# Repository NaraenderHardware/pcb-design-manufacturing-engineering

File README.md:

# PCB Design and Manufacturing Engineering

**Author:** Naraender S  
**License:** [MIT License](LICENSE)  

---

## 1. Overview and Project Scope

This repository documents my engineering work in printed circuit board (PCB) design, schematic capture, circuit calculations, and physical prototyping. It contains four hardware case studies developed using KiCad and practical laboratory fabrication methods:

1. **5V Regulated Through-Hole Power Supply (`designs/general-pcb-design`):** A single-sided linear DC power supply built with through-hole components (LM7805, 1N4007 bridge rectifier, and electrolytic filtering) designed for reliable hand assembly.
2. **Multi-Rail SMD Linear Power Supply (`designs/smd-pcb-design`):** A compact 2-layer surface-mount power distribution board designed to provide +5V, +12V, and -12V rails using TO-252 (DPAK) regulators. *Note: An audit identified a schematic power-rail short in the original design; manufacturing outputs are quarantined, and a preliminary Revision A schematic draft is provided.*
3. **ATtiny85 USB Breakout Dongle (`designs/usb-pcb-design`):** A standalone 2-layer USB development dongle based on the Microchip ATtiny85-20S microcontroller with PCB edge contacts for USB Type-A ports, 3.6V Zener level clamping, and breakout pin headers.
4. **Chemical-Etched Multi-Rail Power Supply Bench Study (`designs/linear-regulator-design`):** A hands-on prototyping project from a hardware workshop demonstrating manual single-sided PCB fabrication using ferric chloride ($FeCl_3$) chemical wet etching, with design calculations and recorded multimeter test readings.

---

## 2. Summary of Case Studies

| Case Study | Architecture / Function | Dimensions | Layer Count | Components | Status Summary | Documentation Link |
| :--- | :--- | :--- | :--- | :--- | :--- | :--- |
| **General THT PCB** | 5V 1.5A Regulated Linear Power Supply | 95.00 x 33.50 mm | 1 Copper Layer (`B.Cu`), 1.6 mm FR4 | 12 parts / 4 mounting holes | Schematic & layout complete; static clearances clean; native ERC/DRC and drill files pending | [Case Study 1 Readme](designs/general-pcb-design/README.md) |
| **SMD Multi-Rail PCB** | Triple-Output (+5V, +12V, -12V) SMD Supply | 33.50 x 30.00 mm | 2 Layers (`F.Cu`, `B.Cu`), 1.6 mm FR4 | 22 parts (DPAK, SMA, 0805) | Critical power-rail short identified; Gerbers quarantined; Revision A is an unverified draft | [Case Study 2 Readme](designs/smd-pcb-design/README.md) |
| **USB ATtiny85 PCB** | ATtiny85-20S USB Breakout Dongle (Standalone) | 40.00 x 12.20 mm | 2 Layers (`F.Cu`, `B.Cu`), 1.6 mm FR4 | 12 parts (SOIC-8, SOD-123) | Schematic & layout complete; static clearances clean; native ERC/DRC and hardware USB checks pending | [Case Study 3 Readme](designs/usb-pcb-design/README.md) |
| **Linear Regulator Bench** | Chemical-Etched (+5V, &plusmn;12V) Bench Prototype | ~100 x 60 mm (Bench) | 1 Layer (Copper-clad single-sided) | Discrete bench parts | Physical workshop prototype; multimeter test readings documented; no digital CAD files | [Case Study 4 Readme](designs/linear-regulator-design/README.md) |

---

## 3. Design Previews and Available Assets

### Case Study 1: 5V Regulated Through-Hole Power Supply
| PCB Layout Preview | Schematic Preview |
| :---: | :---: |
|  |  |

- Schematic: [designs/general-pcb-design/HARDWARE/Kicad-Hardware-Design.kicad_sch](designs/general-pcb-design/HARDWARE/Kicad-Hardware-Design.kicad_sch)
- PCB Layout: [designs/general-pcb-design/HARDWARE/Kicad-Hardware-Design.kicad_pcb](designs/general-pcb-design/HARDWARE/Kicad-Hardware-Design.kicad_pcb)
- Bill of Materials: [designs/general-pcb-design/BOM/bom.csv](designs/general-pcb-design/BOM/bom.csv)
- Bottom Copper Gerber: [designs/general-pcb-design/GERBER/Kicad-Hardware-Design-B_Cu.gbr](designs/general-pcb-design/GERBER/Kicad-Hardware-Design-B_Cu.gbr)

---

### Case Study 2: Multi-Rail SMD Linear Power Supply
| PCB Layout Preview | Schematic Preview |
| :---: | :---: |
|  |  |

- Schematic (Original): [designs/smd-pcb-design/HARDWARE/GitHub2.kicad_sch](designs/smd-pcb-design/HARDWARE/GitHub2.kicad_sch)
- PCB Layout (Original): [designs/smd-pcb-design/HARDWARE/GitHub2.kicad_pcb](designs/smd-pcb-design/HARDWARE/GitHub2.kicad_pcb)
- Bill of Materials: [designs/smd-pcb-design/BOM/bom.csv](designs/smd-pcb-design/BOM/bom.csv)
- Gerber Job File (Quarantined): [designs/smd-pcb-design/GERBER/GitHub2-job.gbrjob](designs/smd-pcb-design/GERBER/GitHub2-job.gbrjob)
- Corrected Draft Schematic: [designs/smd-pcb-design/revA_corrected/HARDWARE/GitHub2_revA_corrected.kicad_sch](designs/smd-pcb-design/revA_corrected/HARDWARE/GitHub2_revA_corrected.kicad_sch)
- Detailed Defect Analysis: [designs/smd-pcb-design/revA_corrected/README.md](designs/smd-pcb-design/revA_corrected/README.md)

---

### Case Study 3: ATtiny85 USB Breakout Dongle
| PCB Layout Preview | Schematic Preview |
| :---: | :---: |
|  |  |

- Schematic: [designs/usb-pcb-design/HARDWARE/USB.kicad_sch](designs/usb-pcb-design/HARDWARE/USB.kicad_sch)
- PCB Layout: [designs/usb-pcb-design/HARDWARE/USB.kicad_pcb](designs/usb-pcb-design/HARDWARE/USB.kicad_pcb)
- Bill of Materials: [designs/usb-pcb-design/BOM/bom.csv](designs/usb-pcb-design/BOM/bom.csv)
- Gerber Job File: [designs/usb-pcb-design/GERBER/USB-job.gbrjob](designs/usb-pcb-design/GERBER/USB-job.gbrjob)

---

### Case Study 4: Chemical-Etched Multi-Rail Power Supply Bench Study

- Design Calculations: [designs/linear-regulator-design/regulator-design/docs/calculations.md](designs/linear-regulator-design/regulator-design/docs/calculations.md)
- Circuit Working Principles: [designs/linear-regulator-design/regulator-design/docs/working.md](designs/linear-regulator-design/regulator-design/docs/working.md)
- Measured Multimeter Readings: [designs/linear-regulator-design/regulator-design/results/readings.txt](designs/linear-regulator-design/regulator-design/results/readings.txt)
- Etching Procedure: [designs/linear-regulator-design/pcb-etching/README.md](designs/linear-regulator-design/pcb-etching/README.md)

---

## 4. Tools, File Formats, and Verification Status

### Confirmed Tools and File Formats
- **KiCad 9:** Used for schematic capture (`.kicad_sch`) and board layout (`.kicad_pcb`).
- **Gerber Files:** Standard RS-274X copper layers (`.gbr`) and Gerber job manifests (`.gbrjob`).
- **Component Data:** Comma-separated Bill of Materials (`.csv`).
- **Vector Previews:** Scalable Vector Graphics (`.svg`) generated directly from CAD layout coordinates.
- **Documentation and Bench Data:** Markdown engineering notes (`.md`) and raw test logs (`.txt`).

### Verification Status and Known Limitations
- **SMD Board Power-Rail Short (Critical Defect):**
  - An unintentional vertical wire (UUID `b3812738-1a62-4d38-bef5-d9db1e02c554`) connects coordinate `(45.72, 35.56)` on the positive DC bus directly to `(45.72, 27.94)` on the 7805 return line in `designs/smd-pcb-design/HARDWARE/GitHub2.kicad_sch`.
  - This short ties regulator `U1` (L7805) input and ground together and shorts filter capacitor `C1`.
  - The board layout in `GitHub2.kicad_pcb` physically routes this shorted net.
  - **The associated manufacturing files are quarantined and must not be used for fabrication.**
  - A preliminary corrected schematic draft is provided in `revA_corrected/`. Excising the shorting wire leaves the 7805 return line floating relative to common ground; this draft remains unverified until connected in KiCad and re-routed on the PCB.
- **Native KiCad ERC and DRC Checks:**
  - KiCad was not installed in the review environment. Python static checks confirmed basic 2D Euclidean clearances between linear copper traces and circular pads, but these do not replace native KiCad Electrical Rules Check (ERC) or Design Rules Check (DRC).
  - Native KiCad ERC and DRC must be executed prior to any commercial manufacturing sign-off.
- **Manufacturing Deliverables:**
  - Complete drill files (`*.drl`), solder mask, and silkscreen Gerber layers are not present locally for the through-hole and USB boards.
- **ATtiny85 USB Dongle Considerations:**
  - The microcontroller uses an internal calibrated RC oscillator. Low-Speed USB 1.1 requires +/-1.5% frequency accuracy, which typically requires runtime software calibration against USB frame packets.
  - The PCB edge connector is designed on 1.60 mm FR4, which may fit loosely in standard USB-A ports (typically expecting a 2.0 mm to 2.4 mm plug tongue).
- **Chemical-Etched Power Supply:**
  - Preserved strictly as a documented hands-on workshop build with recorded multimeter readings; no digital CAD schematic or layout files exist in this repository.

A complete audit log of file hashes, clearance checks, and defect traces is documented in [docs/PORTFOLIO_VERIFICATION.md](docs/PORTFOLIO_VERIFICATION.md).

---

## 5. Repository Structure

```
01_PCB_Design_and_Manufacturing_Engineering/
|-- .gitignore                                    # Excludes editor caches, KiCad backups, and temporary files
|-- LICENSE                                       # MIT License (Naraender S 2025)
|-- README.md                                     # Main repository overview and index
|-- assets/                                       # Vector SVG previews for schematics and layouts
|   |-- general_pcb_layout.svg
|   |-- general_schematic.svg
|   |-- smd_pcb_layout.svg
|   |-- smd_schematic.svg
|   |-- usb_pcb_layout.svg
|   |-- usb_schematic.svg
|   `-- linear_regulator_architecture.svg
|-- docs/
|   `-- PORTFOLIO_VERIFICATION.md                 # Detailed engineering verification report
`-- designs/
    |-- general-pcb-design/                       # Case Study 1: 5V Through-Hole Linear Supply
    |   |-- .gitignore
    |   |-- LICENSE
    |   |-- HISTORICAL_NOTES.md
    |   |-- README.md
    |   |-- pcb_layout.svg & schematic.svg
    |   |-- BOM/bom.csv
    |   |-- GERBER/
    |   |   |-- Kicad-Hardware-Design-B_Cu.gbr
    |   |   `-- Kicad-Hardware-Design-job.gbrjob
    |   `-- HARDWARE/
    |       |-- Kicad-Hardware-Design.kicad_pcb
    |       `-- Kicad-Hardware-Design.kicad_sch
    |-- smd-pcb-design/                           # Case Study 2: Multi-Rail SMD Supply (Defect Documented)
    |   |-- HISTORICAL_NOTES.md
    |   |-- README.md
    |   |-- pcb_layout.svg & schematic.svg
    |   |-- BOM/bom.csv
    |   |-- GERBER/GitHub2-job.gbrjob             # Quarantined manufacturing file
    |   |-- HARDWARE/
    |   |   |-- GitHub2.kicad_pcb
    |   |   `-- GitHub2.kicad_sch
    |   `-- revA_corrected/                       # Unverified Revision A draft schematic
    |       |-- README.md
    |       `-- HARDWARE/GitHub2_revA_corrected.kicad_sch
    |-- usb-pcb-design/                           # Case Study 3: ATtiny85 USB Breakout Dongle
    |   |-- .gitignore
    |   |-- README.md
    |   |-- pcb_layout.svg & schematic.svg
    |   |-- BOM/bom.csv
    |   |-- GERBER/USB-job.gbrjob
    |   `-- HARDWARE/
    |       |-- USB.kicad_pcb
    |       `-- USB.kicad_sch
    `-- linear-regulator-design/                  # Case Study 4: Chemical-Etched Bench Prototype
        |-- HISTORICAL_NOTES.md
        |-- README.md
        |-- architecture.svg
        |-- pcb-etching/
        |   `-- README.md                         # Step-by-step chemical etching guide
        `-- regulator-design/
            |-- README.md
            |-- docs/calculations.md              # Circuit calculations and thermal formulas
            |-- docs/working.md                   # Stage-by-stage circuit operation
            `-- results/readings.txt              # Multimeter voltage readings
```

---

## 6. License

This project and all hardware designs, documentation, and test logs are licensed under the [MIT License](LICENSE).  
Copyright &copy; 2025 **Naraender S**.

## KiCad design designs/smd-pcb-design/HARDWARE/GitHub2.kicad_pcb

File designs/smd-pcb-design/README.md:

# Case Study 2: Multi-Rail SMD Linear Power Supply

**Design Type:** Multi-Rail Linear Power Distribution (Surface-Mount)  
**CAD Tool:** KiCad  
**Status:** Defect identified during audit; manufacturing outputs quarantined; Revision A is an unverified draft schematic  

---

## 1. Overview and Design Purpose

This project is a surface-mount power supply board designed to deliver three regulated DC voltage rails: +5V, +12V, and -12V in a compact 33.5 mm x 30.0 mm footprint. The intended architecture takes a dual-polarity center-tapped AC transformer input or dual-polarity DC input to drive:
- An **L7805** regulator for a +5V logic rail
- An **L7812** regulator for a +12V analog/relay rail
- An **L7912** regulator for a -12V negative rail (such as for dual-supply operational amplifiers)

All three regulators use surface-mount DPAK (TO-252) packages, paired with SMA rectifier diodes and SMD electrolytic capacitors to keep the board compact.

---

## 2. Circuit Architecture and Schematics

### Schematic Preview

The schematic uses a 3-pin input header (`J1`), a 4-diode rectifier bridge (`D1`–`D4`), bulk filter capacitors (`C1`, `C2`, `C3`), high-frequency ceramic bypass capacitors (`C4`, `C5`, `C6`), three linear regulators (`U1`, `U2`, `U3`), output filter capacitors (`C7`–`C12`), and JST-PH output headers (`J2`, `J3`).

---

## 3. PCB Layout Architecture

### PCB Layout Preview

- **Dimensions:** 33.50 mm x 30.00 mm (finished profile 33.55 mm x 30.05 mm)
- **Layer Count:** 2 copper layers (`F.Cu`, `B.Cu`)
- **Substrate Thickness:** 1.60 mm FR4
- **Vias:** 16 interlayer vias (0.60 mm pad diameter, 0.30 mm finished drill hole)

---

## 4. Defect Analysis: Power-Rail Short Circuit

During an engineering audit of the design files, a critical schematic drafting mistake was identified that propagated directly into the PCB layout:

### Description of the Defect
In the original schematic file (`HARDWARE/GitHub2.kicad_sch`), an unintended vertical wire segment was drawn at `x=45.72` between `y=35.56` and `y=27.94` (UUID `b3812738-1a62-4d38-bef5-d9db1e02c554`):
- Point `(45.72, 35.56)` lies on the unregulated positive DC rail feeding regulator `U2` (L7812) from diode bridge cathodes `D1`/`D3`.
- Point `(45.72, 27.94)` lies on the ground return line for regulator `U1` (L7805).
- Because this vertical wire connected the two lines, KiCad merged the unregulated positive rail and the 7805 return line into a single net: `Net-(D1-K)`.

### Impact on Layout and Physical Circuit
1. **Regulator `U1` (L7805):** Pin 1 (Vin) and Pin 2 (GND) are shorted together on the same net.
2. **Capacitor `C1` (Bulk Filter):** Both positive and negative terminals are connected to `Net-(D1-K)`, shorting the capacitor across its terminals.
3. **Capacitor `C4` (Ceramic Bypass):** Both terminals are tied to `Net-(D1-K)`.
4. **Output Capacitors `C7` and `C10`:** Ground return terminals are tied to raw positive DC rather than common ground.
5. **Connector `J2` (5V Output):** Pin 2 (return) is tied to raw positive DC.
6. **Rectifier Stage:** Diodes `D1` and `D3` discharge directly into the 7805 return line.

### Manufacturing and Safety Impact
If this board were fabricated and powered as routed:
- It would present a direct dead short across the rectified DC power source.
- Diodes would fail from overcurrent, copper traces could burn, or the power supply would trigger overcurrent protection.
- **Quarantine Notice:** The Gerber files in `GERBER/` are **quarantined and must not be used for fabrication**.

---

## 5. Revision A Draft and Current Status

To preserve the authentic historical design files, the original schematic and PCB files in `HARDWARE/` remain completely unchanged.

A preliminary corrected schematic is provided in `revA_corrected/`:
- **File:** [revA_corrected/HARDWARE/GitHub2_revA_corrected.kicad_sch](revA_corrected/HARDWARE/GitHub2_revA_corrected.kicad_sch)
- **Detailed Documentation:** [revA_corrected/README.md](revA_corrected/README.md)
- **Change Made:** The vertical shorting wire (UUID `b3812738-1a62-4d38-bef5-d9db1e02c554`) was excised, restoring the continuous positive rail feeding `U2`.

### Remaining Unresolved Issues in Revision A
1. **Floating Return Rail:** Excising the shorting wire eliminates the dead short, but leaves the 7805 return rail (`y=27.94`) completely floating with no electrical connection to the Common Ground rail (`y=49.53`).
2. **PCB Layout Unchanged:** Modifying the schematic does not automatically reroute the copper traces in `HARDWARE/GitHub2.kicad_pcb`. The physical board layout still contains shorted copper traces.
3. **Draft Status:** Revision A is an **unverified draft**. Before this board can be fabricated, the return rail must be connected to ground in KiCad, traces must be rerouted in the PCB editor, and native ERC and DRC checks must pass.

---

## 6. Bill of Materials

| Reference | Quantity | Value | Package / Footprint | Description |
| :--- | :--- | :--- | :--- | :--- |
| `C1, C2, C3, C7, C8, C9` | 6 | Polarized Cap (SMD) | `Capacitor_SMD:CP_Elec_6.3x5.8` | Bulk filtering per voltage rail |
| `C4, C5, C6, C10, C11, C12` | 6 | Ceramic Cap (SMD) | `Capacitor_SMD:C_0805_2012Metric` | High-frequency bypass per rail |
| `D1, D2, D3, D4` | 4 | 1N4007 (SMD) | `Diode_SMD:D_SMA` | 1A 1000V Rectifier diodes |
| `J1, J3` | 2 | Conn_01x03 | `Connector_JST:JST_PH_S3B-PH-SM4-TB_1x03` | 3-pin JST-PH power interface |
| `J2` | 1 | Conn_01x02 | `Connector_JST:JST_PH_S2B-PH-SM4-TB_1x02` | 2-pin JST-PH 5V output interface |
| `U1` | 1 | L7805 | `Package_TO_SOT_SMD:TO-252-2` | +5V SMD linear regulator (DPAK) |
| `U2` | 1 | L7812 | `Package_TO_SOT_SMD:TO-252-2` | +12V SMD linear regulator (DPAK) |
| `U3` | 1 | L7912 | `Package_TO_SOT_SMD:TO-252-2` | -12V SMD linear regulator (DPAK) |

---

## 7. Project Files

- Original Schematic: [HARDWARE/GitHub2.kicad_sch](HARDWARE/GitHub2.kicad_sch)
- Original PCB Layout: [HARDWARE/GitHub2.kicad_pcb](HARDWARE/GitHub2.kicad_pcb)
- Bill of Materials: [BOM/bom.csv](BOM/bom.csv)
- Gerber Job File (Quarantined): [GERBER/GitHub2-job.gbrjob](GERBER/GitHub2-job.gbrjob)
- Historical Design Notes: [HISTORICAL_NOTES.md](HISTORICAL_NOTES.md)
- Corrected Revision A Draft: [revA_corrected/README.md](revA_corrected/README.md)

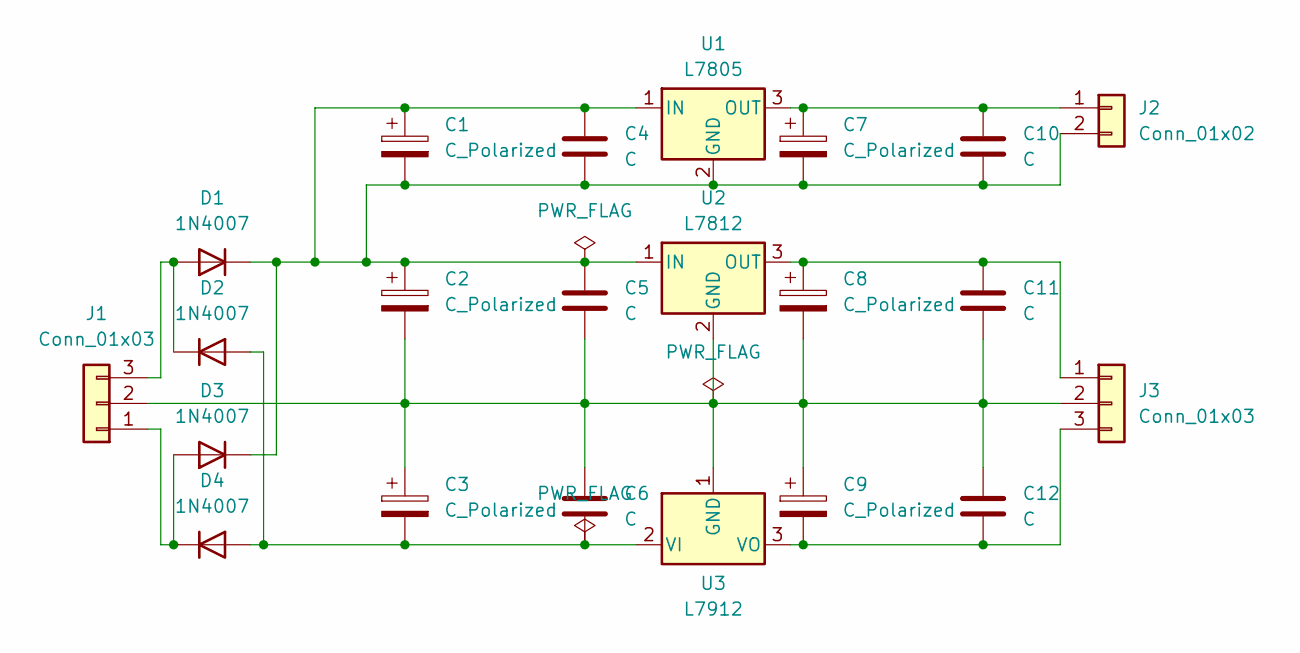
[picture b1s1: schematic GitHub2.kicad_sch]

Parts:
C1, C2, C3, C7, C8, C9: C_Polarized; CP_Elec_6.3x5.8
C4, C5, C6, C10, C11, C12: C; C_0805_2012Metric
D1, D2, D3, D4: 1N4007; D_SMA
J1, J3: Conn_01x03; JST_PH_S3B-PH-SM4-TB_1x03-1MP_P2.00mm_Horizontal
J2: Conn_01x02; JST_PH_S2B-PH-SM4-TB_1x02-1MP_P2.00mm_Horizontal
U1: L7805; TO-252-2
U2: L7812; TO-252-2
U3: L7912; TO-252-2

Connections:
unnamed: D1.2 (A), D2.1 (K), J1.3
unnamed: C1.1, C1.2, C2.1, C4.1, C4.2, C5.1, C7.2, C10.2, D1.1 (K), D3.1 (K), J2.2, U1.1 (IN), U1.2 (GND), U2.1 (IN)
unnamed: C3.2, C6.2, D2.2 (A), D4.2 (A), U3.2 (VI)
unnamed: D3.2 (A), D4.1 (K), J1.1
unnamed: C2.2, C3.1, C5.2, C6.1, C8.2, C9.1, C11.2, C12.1, J1.2, J3.2, U2.2 (GND), U3.1 (GND)
unnamed: C7.1, C10.1, J2.1, U1.3 (OUT)
unnamed: C8.1, C11.1, J3.1, U2.3 (OUT)
unnamed: C9.2, C12.2, J3.3, U3.3 (VO)

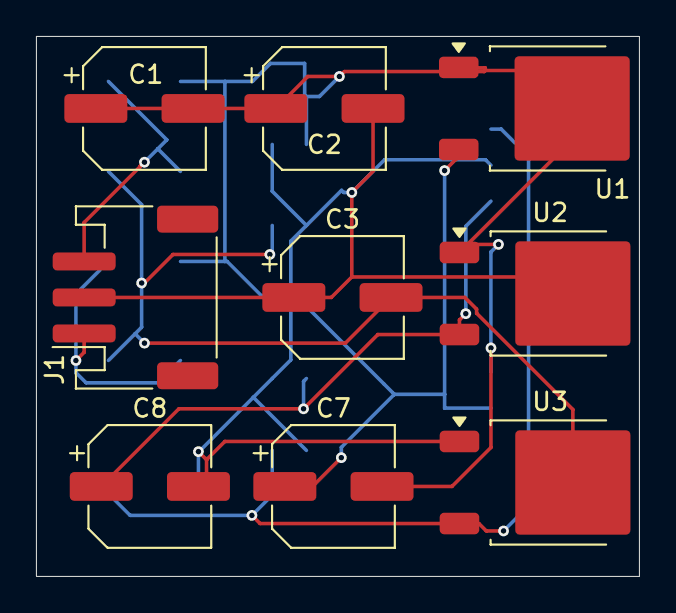
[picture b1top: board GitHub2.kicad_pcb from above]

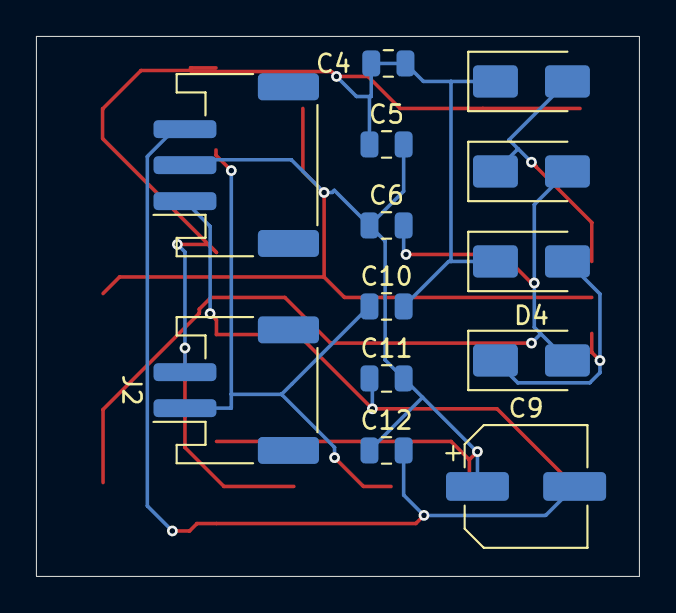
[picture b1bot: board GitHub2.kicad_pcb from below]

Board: 2 copper layers, 33.5 x 30.0 mm, 22 parts (13 on the bottom side), 8 nets.

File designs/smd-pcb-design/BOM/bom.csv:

"Reference","Qty","Value","DNP","Exclude from BOM","Exclude from Board","Footprint","Datasheet"
"C1,C2,C3,C7,C8,C9","6","C_Polarized","","","","Capacitor_SMD:CP_Elec_6.3x5.8","~"
"C4,C5,C6,C10,C11,C12","6","C","","","","Capacitor_SMD:C_0805_2012Metric","~"
"D1,D2,D3,D4","4","1N4007","","","","Diode_SMD:D_SMA","http://www.vishay.com/docs/88503/1n4001.pdf"
"J1,J3","2","Conn_01x03","","","","Connector_JST:JST_PH_S3B-PH-SM4-TB_1x03-1MP_P2.00mm_Horizontal","~"
"J2","1","Conn_01x02","","","","Connector_JST:JST_PH_S2B-PH-SM4-TB_1x02-1MP_P2.00mm_Horizontal","~"
"U1","1","L7805","","","","Package_TO_SOT_SMD:TO-252-2","http://www.st.com/content/ccc/resource/technical/document/da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"
"U2","1","L7812","","","","Package_TO_SOT_SMD:TO-252-2","http://www.st.com/content/ccc/resource/technical/document/da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"
"U3","1","L7912","","","","Package_TO_SOT_SMD:TO-252-2","http://www.st.com/content/ccc/resource/technical/document/da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"

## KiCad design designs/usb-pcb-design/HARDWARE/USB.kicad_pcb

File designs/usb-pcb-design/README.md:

# Case Study 3: ATtiny85 USB Breakout Dongle

**Design Type:** Embedded Microcontroller / Low-Speed USB 1.1 Development Dongle  
**CAD Tool:** KiCad  
**Status:** Schematic and PCB layout complete; static geometry checks clean; native KiCad ERC/DRC and hardware USB compliance validation pending  

---

## 1. Overview and Design Purpose

In this project, I designed a miniature USB development dongle based on the Microchip **ATtiny85-20S** 8-bit AVR microcontroller in an SOIC-8 package. The board plugs directly into a standard USB Type-A port and is designed for bit-banged USB communication (such as the V-USB library or Micronucleus bootloader), allowing firmware flashing and basic USB HID or CDC communication without an external USB-to-UART bridge IC.

This board is an independent, standalone development platform.

```
+-------------------------------------------------------------------------+
| [USB Plug]     [Zener Clamps]     [ATtiny85 MCU]     [Breakout Headers] |
|                                                                         |
| Pin 1: +5V  --------------------> VCC (Pin 8)  ---> J1 Pin 1 (+5V)      |
| Pin 2: D-   ---> [68R] + [3V6] -> PB3 (Pin 2)  ---> J2 Pin 3 (PB3)      |
| Pin 3: D+   ---> [68R] + [3V6] -> PB4 (Pin 3)  ---> J2 Pin 2 (PB4)      |
| Pin 4: GND  --------------------> GND (Pin 4)  ---> J2 Pin 1 (GND)      |
+-------------------------------------------------------------------------+
```

---

## 2. Circuit Architecture and Schematics

### Schematic Preview

The circuit comprises six main sub-circuits:

1. **USB Type-A Interface (`U2`):** Direct PCB edge contacts shaped to mate with standard USB Type-A female receptacles.
2. **Voltage Clamping and Level Translation (`D2`, `D3`, `R2`, `R3`):**
   - Standard USB data lines operate at 3.3V, but the ATtiny85 runs at 5.0V directly from USB VBUS.
   - Dual 3.6V Zener diodes (`D2`, `D3` in SOD-123 packages) clamp the logic high levels on D+ and D- to prevent damage to host transceivers.
   - 68 ohm series damping resistors (`R2`, `R3` in 0603 packages) match line impedance and limit transient current spikes.
3. **USB Low-Speed Enumeration (`R4`):**
   - A 1.0 k-ohm pull-up resistor from D- to +5V signals Low-Speed (1.5 Mbps) USB device presence to the host USB hub upon connection.
4. **Power Decoupling (`C1`):**
   - A 100 nF 0603 ceramic capacitor is placed next to VCC (pin 8) and GND (pin 4) to filter high-frequency switching noise.
5. **Status LED (`D1`, `R1`):**
   - An 0603 surface-mount LED in series with a 330 ohm resistor is connected to PB1 (pin 6) for power or debug indication.
6. **I/O Breakout Headers (`J1`, `J2`):**
   - Dual 1x4 2.54 mm pin headers break out all ATtiny85 pins:
     - `J2`: GND, PB3, PB4, PB5 (Reset)
     - `J1`: +5V, PB2 (SCK/SCL), PB1 (MISO), PB0 (MOSI/SDA)

---

## 3. PCB Layout Architecture

### PCB Layout Preview

- **Dimensions:** 40.00 mm x 12.20 mm (40.05 mm x 12.25 mm in Gerber profile)
- **Substrate:** Standard 1.60 mm FR4
- **Layers:** 2 copper layers (`F.Cu`, `B.Cu`)
- **Vias:** 9 vias (0.60 mm pad diameter, 0.30 mm finished drill hole)
- **Clearances:** Minimum track-to-track clearance is 0.2017 mm (7.94 mil); minimum pad-to-track clearance is 0.2026 mm (7.98 mil)

---

## 4. Verification Status and Engineering Considerations

### Confirmed CAD Facts
- **Schematic-to-Layout Match:** All 12 physical components match between the schematic symbols, PCB footprints, and BOM.
- **Routing:** All 11 active electrical nets are routed with zero unrouted ratsnest lines and no overlapping copper shorts.
- **Static Clearance Benchmark:** Minimum track clearances exceed 0.1524 mm (6 mil).

### Known Limitations and Hardware Risks
While the CAD netlist and layout geometry are consistent, several hardware aspects require validation before this design could be used reliably in production:

1. **Clock Stability and USB Timing:**
   - The ATtiny85 is wired to run off its internal RC oscillator (no external crystal or resonator is present).
   - The USB 1.1 Low-Speed specification requires a clock frequency accuracy within +/-1.5% (1.5 Mbps +/- 22.5 kbps).
   - An uncalibrated internal RC oscillator can drift by more than +/-2% over temperature and voltage. Reliable enumeration requires software-based calibration (e.g., locking to USB Start-of-Frame tokens).
2. **Zener Diode Junction Capacitance:**
   - The 3.6V Zener diodes (`D2`, `D3`) add parasitic junction capacitance (typically 30 pF to 100 pF).
   - Combined with the 68 ohm series resistors, this capacitance slows rise/fall times and could degrade signal integrity margins on some USB host controllers.
3. **PCB Edge Connector Thickness:**
   - The USB plug is formed directly on the 1.60 mm FR4 substrate.
   - Standard USB Type-A plugs specify a tongue thickness of 2.00 mm to 2.40 mm. A 1.60 mm board may fit loosely in some sockets, which could lead to intermittent contact.
4. **VBUS Protection:**
   - The board does not include an onboard polyfuse (PTC) or TVS diode on the +5V VBUS line, relying on host-side overcurrent protection.
5. **Toolchain Status:**
   - Native KiCad ERC and DRC checks were not run in this audit environment because KiCad was not installed locally.

---

## 5. Bill of Materials

| Reference | Quantity | Value | Footprint | Description |
| :--- | :--- | :--- | :--- | :--- |
| `C1` | 1 | 100 nF | `Capacitor_SMD:C_0603_1608Metric` | VCC high-frequency decoupling capacitor |
| `D1` | 1 | LED | `LED_SMD:LED_0603_1608Metric` | Status indicator LED |
| `D2, D3` | 2 | 3V6 Zener | `Diode_SMD:D_SOD-123` | USB D+/D- 3.6V voltage clamp diodes |
| `J1` | 1 | 1x4 Header | `Connector_PinHeader_2.54mm:PinHeader_1x04` | Breakout header (pins 5, 6, 7, 8) |
| `J2` | 1 | 1x4 Header | `Connector_PinHeader_2.54mm:PinHeader_1x04` | Breakout header (pins 1, 2, 3, 4) |
| `R1` | 1 | 330 ohm | `Resistor_SMD:R_0603_1608Metric` | Current-limiting resistor for LED |
| `R2, R3` | 2 | 68 ohm | `Resistor_SMD:R_0603_1608Metric` | USB series damping / impedance matching |
| `R4` | 1 | 1.0 k-ohm | `Resistor_SMD:R_0603_1608Metric` | D- pull-up resistor for Low-Speed USB |
| `U1` | 1 | ATtiny85-20S | `Package_SO:SOIC-8_5.3x5.3mm_P1.27mm` | 8-bit AVR microcontroller |
| `U2` | 1 | USB Type-A | `Connector_USB:USB` | PCB edge USB Type-A connector |

---

## 6. Project Files

- Schematic: [HARDWARE/USB.kicad_sch](HARDWARE/USB.kicad_sch)
- PCB Layout: [HARDWARE/USB.kicad_pcb](HARDWARE/USB.kicad_pcb)
- Bill of Materials: [BOM/bom.csv](BOM/bom.csv)
- Gerber Job File: [GERBER/USB-job.gbrjob](GERBER/USB-job.gbrjob)

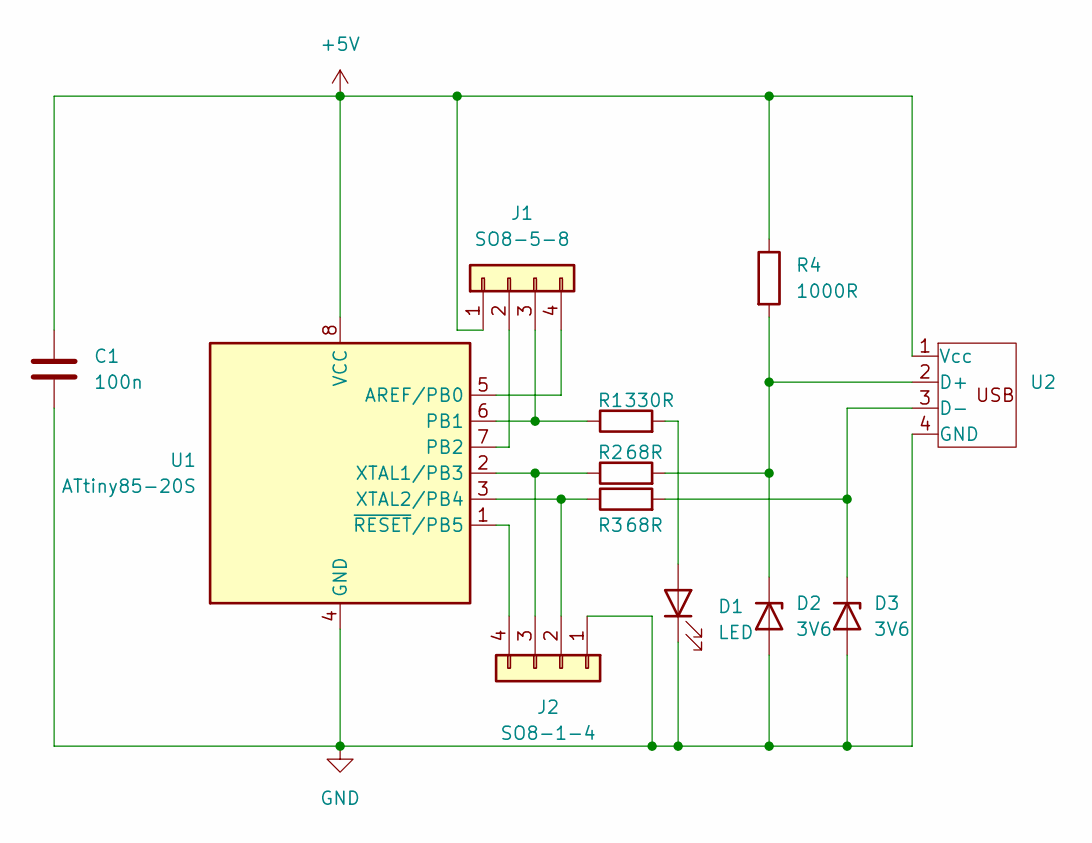
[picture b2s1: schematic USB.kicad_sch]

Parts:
C1: 100n; C_0603_1608Metric
D1: LED; LED_0603_1608Metric
D2, D3: 3V6; D_SOD-123
J1: SO8-5-8; PinHeader_1x04_P2.54mm_Horizontal
J2: SO8-1-4; PinHeader_1x04_P2.54mm_Horizontal
R1: 330R; R_0603_1608Metric
R2, R3: 68R; R_0603_1608Metric
R4: 1000R; R_0603_1608Metric
U1: ATtiny85-20S; SOIC-8_5.3x5.3mm_P1.27mm
U2: USB

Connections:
+5V: C1.1, J1.1, R4.1, U1.8 (VCC), U2.1 (Vcc)
GND: C1.2, D1.1 (K), D2.2 (A), D3.2 (A), J2.1, U1.4 (GND), U2.4 (GND)
unnamed: D1.2 (A), R1.2
unnamed: D2.1 (K), R2.2, R4.2, U2.2 (D+)
unnamed: D3.1 (K), R3.2, U2.3 (D-)
unnamed: J1.2, U1.7 (PB2)
unnamed: J1.3, R1.1, U1.6 (PB1)
unnamed: J1.4, U1.5 (AREF/PB0)
unnamed: J2.2, R3.1, U1.3 (XTAL2/PB4)
unnamed: J2.3, R2.1, U1.2 (XTAL1/PB3)
unnamed: J2.4, U1.1 (~RESET/PB5)

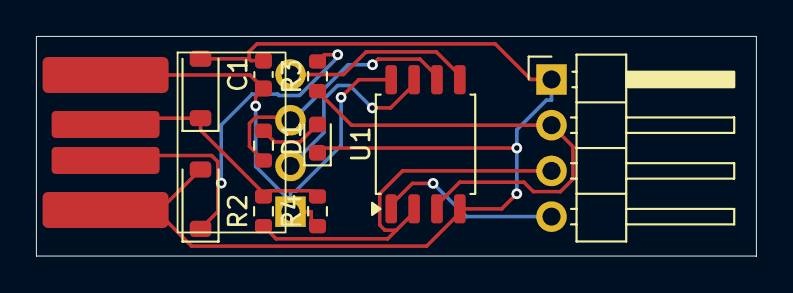
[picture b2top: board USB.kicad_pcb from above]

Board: 2 copper layers, 40.0 x 12.2 mm, 12 parts (1 on the bottom side), 11 nets.

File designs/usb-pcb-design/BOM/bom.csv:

"Reference","Qty","Value","DNP","Exclude from BOM","Exclude from Board","Footprint","Datasheet"
"C1","1","100n","","","","Capacitor_SMD:C_0603_1608Metric","~"
"D1","1","LED","","","","LED_SMD:LED_0603_1608Metric","~"
"D2,D3","2","3V6","","","","Diode_SMD:D_SOD-123","~"
"J1","1","SO8-5-8","","","","Connector_PinHeader_2.54mm:PinHeader_1x04_P2.54mm_Horizontal","~"
"J2","1","SO8-1-4","","","","Connector_PinHeader_2.54mm:PinHeader_1x04_P2.54mm_Horizontal","~"
"R1","1","330R","","","","Resistor_SMD:R_0603_1608Metric","~"
"R2,R3","2","68R","","","","Resistor_SMD:R_0603_1608Metric","~"
"R4","1","1000R","","","","Resistor_SMD:R_0603_1608Metric","~"
"U1","1","ATtiny85-20S","","","","Package_SO:SOIC-8_5.3x5.3mm_P1.27mm","http://ww1.microchip.com/downloads/en/DeviceDoc/atmel-2586-a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"
"U2","1","~","","","","Connector_USB:USB",""

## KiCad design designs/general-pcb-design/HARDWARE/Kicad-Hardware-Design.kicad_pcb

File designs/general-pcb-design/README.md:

# Case Study 1: 5V Regulated Through-Hole Power Supply

**Design Type:** Linear DC Power Supply (Through-Hole)  
**CAD Tool:** KiCad 9  
**Status:** Schematic and PCB layout complete; static geometry checks clean; native KiCad ERC/DRC and complete drill files pending  

---

## 1. Overview and Design Purpose

In this project, I designed a 5V DC regulated linear power supply using through-hole technology (THT). The board converts an AC input from a step-down transformer or an unregulated DC input into a stable +5V DC rail suitable for breadboards, logic ICs, or microcontroller circuits.

I chose through-hole components (TO-220 package for the regulator, DO-41 for diodes, and radial lead capacitors) and single-sided copper routing on the bottom layer (`B.Cu`) so the board can be assembled easily by hand or fabricated using single-sided prototyping methods.

```
+------------+     +-------------------+     +------------------+     +-----------------+     +------------+
| AC/DC In   | --> | 4x 1N4007 Bridge  | --> | Bulk Filter      | --> | LM7805 TO-220   | --> | 5V Output  |
| Terminal   |     | Full-Wave Rect.   |     | Electrolytic Cap |     | Linear Reg. IC  |     | Terminal   |
+------------+     +-------------------+     +------------------+     +-----------------+     +------------+
                                                                             |
                                                                             v
                                                                      +-----------------+
                                                                      | LED Indicator   |
                                                                      +-----------------+
```

---

## 2. Circuit Stages and Operation

### Schematic Preview

The circuit consists of six functional stages:

1. **Input Interface (`J1`):** A 2-pin Phoenix Contact MKDS 1,5/2 horizontal screw terminal block (5.00 mm pitch) connects the AC secondary winding or unregulated DC input.
2. **Bridge Rectification (`D1`, `D2`, `D3`, `D4`):** Four 1N4007 silicon rectifier diodes (1A, 1000V) in DO-41 packages form a full-wave bridge rectifier. For AC input, two diodes conduct per half-cycle, producing pulsating DC with a total diode drop of approximately 1.4V.
3. **Filtering Network (`C1`, `C2`):**
   - `C1`: A 1000 uF radial electrolytic capacitor smooths low-frequency 100 Hz/120 Hz rectifier ripple.
   - `C2`: A 100 nF ceramic disc capacitor placed close to the regulator input filters high-frequency noise and prevents parasitic oscillation.
4. **Linear Voltage Regulation (`U1`):** An LM7805 fixed positive linear regulator in a TO-220-3 vertical package steps the filtered DC voltage down to +5V. It requires at least 7V input for proper regulation (2V dropout headroom).
5. **Output Filtering (`C3`):** A 100 uF electrolytic capacitor stabilizes the +5V output rail during load steps.
6. **Power Indicator (`D5`, `R1`):** A 5 mm flat-top LED in series with a 330 ohm axial resistor provides a visual indication that the 5V rail is powered.

---

## 3. PCB Layout and Mechanical Details

### PCB Layout Preview

- **Dimensions:** 95.00 mm x 33.50 mm (95.05 mm x 33.55 mm in Gerber profile).
- **Substrate:** Standard 1.60 mm FR4.
- **Copper Layers:** Single-sided routing on the Bottom Copper layer (`B.Cu`). Through-hole components mount on the top side (`F.Cu`).
- **Traces:** Standard signal and power traces with dedicated wide copper tracks for ground return.
- **Mounting:** 4 unplated 3.5 mm mounting holes located at the corners for chassis standoffs.

---

## 4. Verification Status and Limitations

- **Netlist Consistency:** All 12 electrical components in the schematic correlate directly with footprints in the PCB layout file.
- **Static Clearance Checks:** A custom Python geometry analysis of the KiCad file confirmed:
  - Minimum track-to-track clearance: 0.8607 mm (exceeds the 0.1524 mm / 6 mil baseline).
  - Minimum pad-to-track clearance: 0.6000 mm (measured to pad J2.2, which is circular and exact in linear segment scope).
  - No short circuits detected across distinct nets.
- **Important Limitations:**
  - Python static checks only evaluate linear 2D copper clearances; they do not replace native KiCad Electrical Rules Check (ERC) or Design Rules Check (DRC).
  - Native KiCad ERC and DRC have not been run in this environment because KiCad is not installed locally.
  - The local `GERBER/` folder contains only the bottom copper layer (`Kicad-Hardware-Design-B_Cu.gbr`) and the job file (`Kicad-Hardware-Design-job.gbrjob`). Drill files (`PTH.drl`, `NPTH.drl`), solder mask, and silkscreen layers are not present locally.
  - The board should not be sent for commercial manufacturing until native KiCad DRC is executed and a full manufacturing archive (drill and mask layers) is generated.

---

## 5. Bill of Materials

| Reference | Quantity | Value | Package / Footprint | Description |
| :--- | :--- | :--- | :--- | :--- |
| `C1` | 1 | 1000 uF | `Capacitor_THT:CP_Radial_D12.5mm_P5.00mm` | Bulk electrolytic filter capacitor |
| `C2` | 1 | 100 nF | `Capacitor_THT:C_Disc_D4.7mm_W2.5mm_P5.00mm` | High-frequency ceramic bypass capacitor |
| `C3` | 1 | 100 uF | `Capacitor_THT:CP_Radial_D8.0mm_P5.00mm` | Output stabilization capacitor |
| `D1, D2, D3, D4` | 4 | 1N4007 | `Diode_THT:D_DO-41_SOD81_P10.16mm_Horizontal` | 1000V 1A Silicon rectifier diodes |
| `D5` | 1 | LED | `LED_THT:LED_D5.0mm_FlatTop` | Power status indicator |
| `J1, J2` | 2 | Conn_01x02 | `TerminalBlock_Phoenix:MKDS-1,5-2_1x02_P5.00mm` | Input and output screw terminals |
| `R1` | 1 | 330 ohm | `Resistor_THT:R_Axial_DIN0411_L9.9mm_D3.6mm` | Current-limiting resistor for LED |
| `U1` | 1 | LM7805 | `Package_TO_SOT_THT:TO-220-3_Vertical` | Fixed +5V linear regulator |

---

## 6. Project Files

- Schematic: [HARDWARE/Kicad-Hardware-Design.kicad_sch](HARDWARE/Kicad-Hardware-Design.kicad_sch)
- PCB Layout: [HARDWARE/Kicad-Hardware-Design.kicad_pcb](HARDWARE/Kicad-Hardware-Design.kicad_pcb)
- Bill of Materials: [BOM/bom.csv](BOM/bom.csv)
- Gerber Job File: [GERBER/Kicad-Hardware-Design-job.gbrjob](GERBER/Kicad-Hardware-Design-job.gbrjob)
- Bottom Copper Gerber: [GERBER/Kicad-Hardware-Design-B_Cu.gbr](GERBER/Kicad-Hardware-Design-B_Cu.gbr)
- Historical Design Notes: [HISTORICAL_NOTES.md](HISTORICAL_NOTES.md)

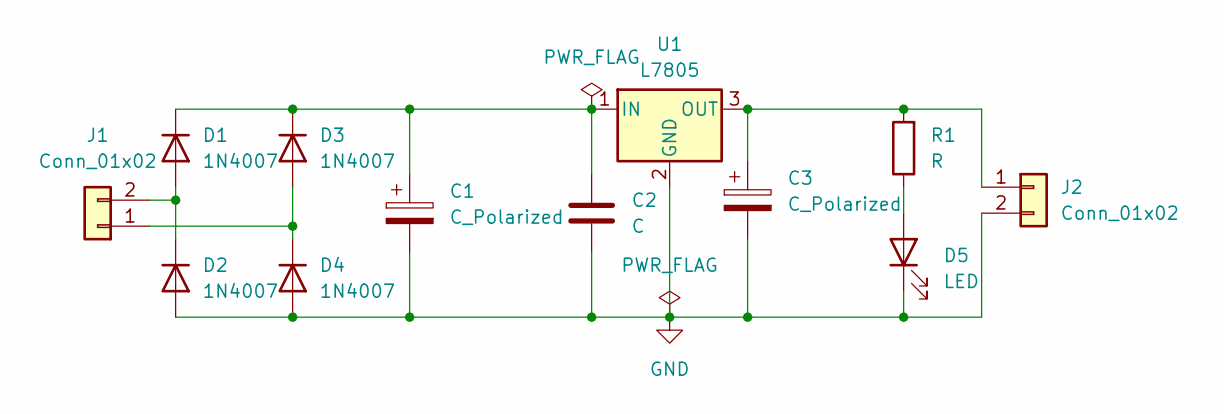
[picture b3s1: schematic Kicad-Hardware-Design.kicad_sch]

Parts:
C1: C_Polarized; CP_Radial_D12.5mm_P5.00mm
C2: C; C_Disc_D4.7mm_W2.5mm_P5.00mm
C3: C_Polarized; CP_Radial_D8.0mm_P5.00mm
D1, D2, D3, D4: 1N4007; D_DO-41_SOD81_P10.16mm_Horizontal
D5: LED; LED_D5.0mm_FlatTop
J1, J2: Conn_01x02; TerminalBlock_Phoenix_MKDS-1,5-2_1x02_P5.00mm_Horizontal
R1: R; R_Axial_DIN0411_L9.9mm_D3.6mm_P20.32mm_Horizontal
U1: L7805; TO-220-3_Vertical

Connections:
GND: C1.2, C2.2, C3.2, D2.2 (A), D4.2 (A), D5.1 (K), J2.2, U1.2 (GND)
unnamed: D1.2 (A), D2.1 (K), J1.2
unnamed: C1.1, C2.1, D1.1 (K), D3.1 (K), U1.1 (IN)
unnamed: D3.2 (A), D4.1 (K), J1.1
unnamed: D5.2 (A), R1.1
unnamed: C3.1, J2.1, R1.2, U1.3 (OUT)

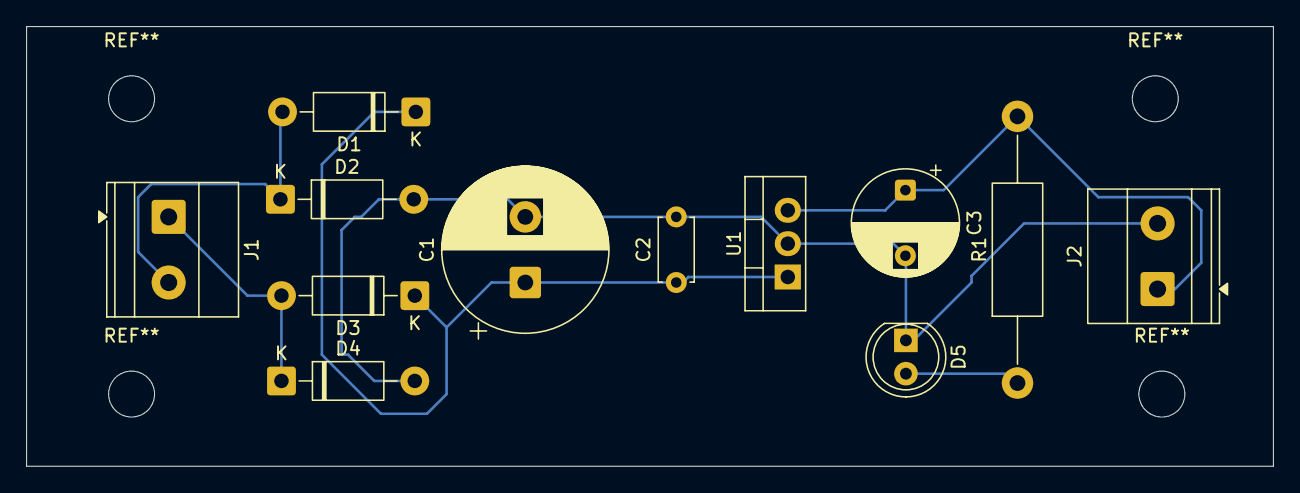
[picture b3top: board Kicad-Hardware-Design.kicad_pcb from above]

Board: 2 copper layers, 95.0 x 33.5 mm, 12 parts (0 on the bottom side), 6 nets.
